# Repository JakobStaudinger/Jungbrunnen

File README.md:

# Jungbrunnen
An embedded project using a Raspberry Pi Pico to strobe LEDs to make it look like water droplets are floating in mid-air.
Heavily inspired by [isaac879's RGB Time Fountain](https://github.com/isaac879/RGB-Time-Fountain)

> [!WARNING]
> 🚧 Under development 🚧

## Firmware
Firmware for the cyw43 chip can be found [here](https://github.com/embassy-rs/embassy/tree/main/cyw43-firmware). It should be placed in the `cyw43-firmware` folder to make the program compile.

### Dev Firmware
To reduce the time it takes to flash the program to the Pico, you can enable the `dev_firmware` feature. This makes it so the firmware doesn't get embedded into the binary, and instead the program assumes it is already located at a fixed memory address.

You need to ensure the firmware is actually pre-baked into the flash memory. To do this, use the `probe-rs download` command, like so:
```console
$ probe-rs download cyw43-firmware/43439A0.bin --binary-format bin --chip RP2040 --base-address 0x10100000
$ probe-rs download cyw43-firmware/43439A0_clm.bin --binary-format bin --chip RP2040 --base-address 0x10140000
```

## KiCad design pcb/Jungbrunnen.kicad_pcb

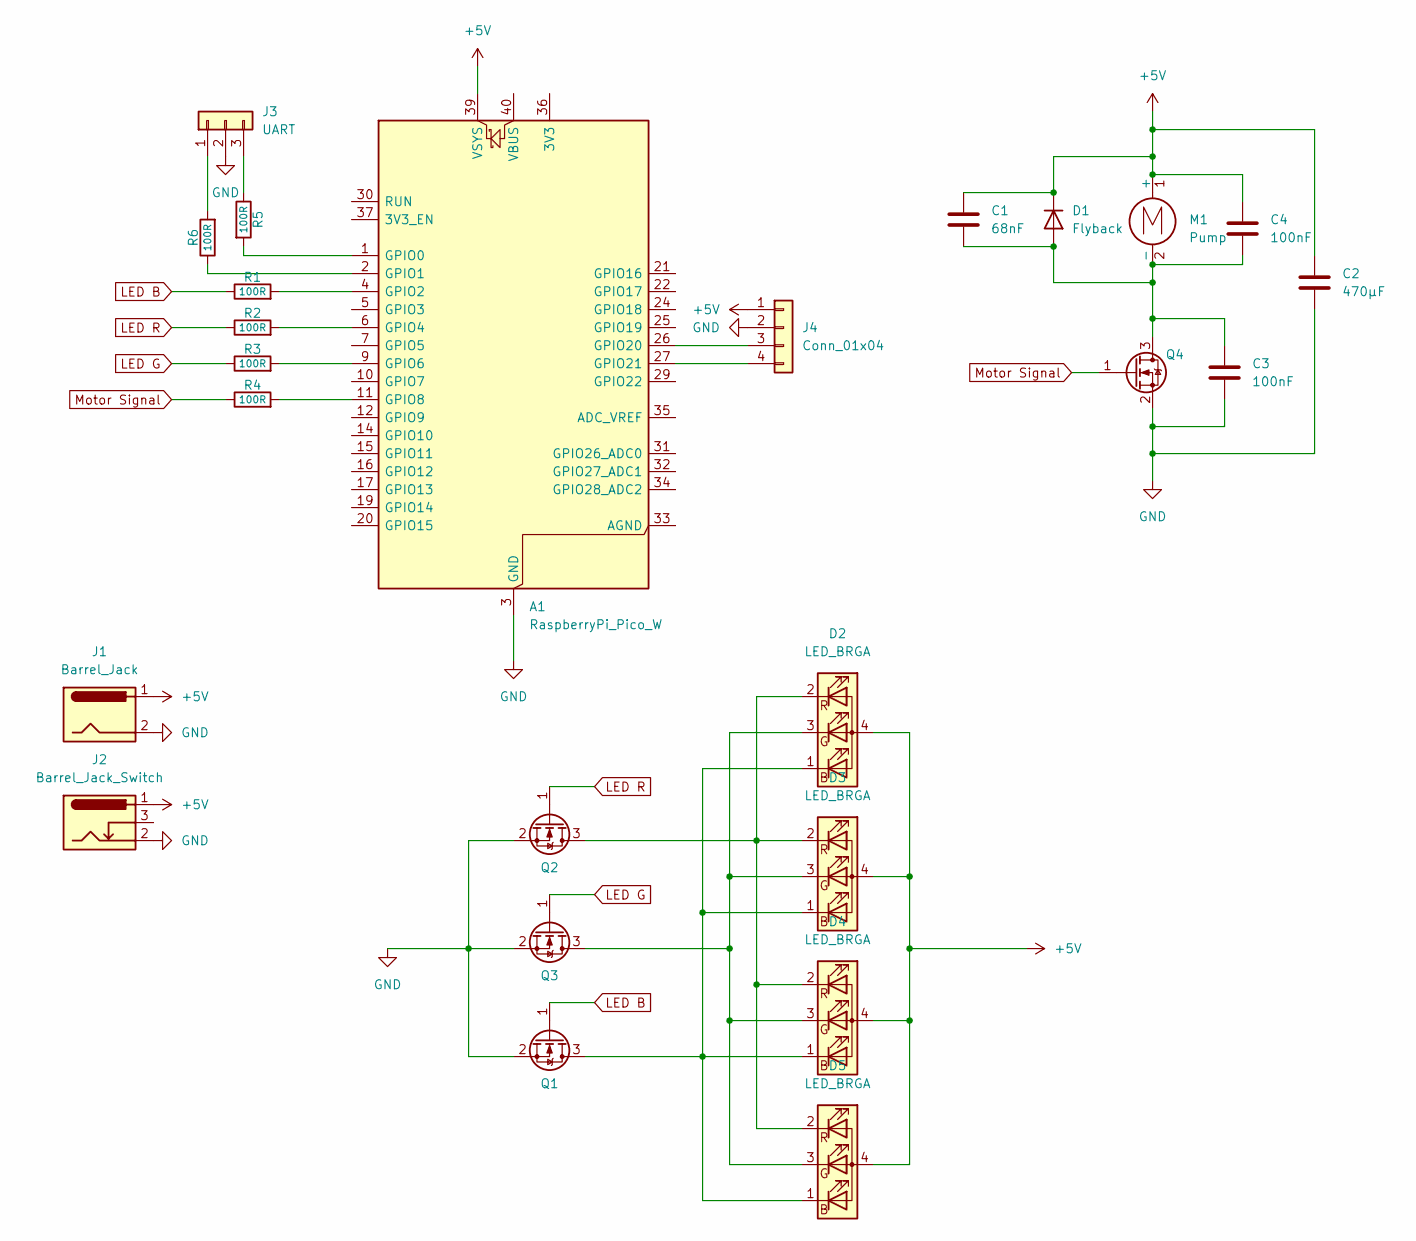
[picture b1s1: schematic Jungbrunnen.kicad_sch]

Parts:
A1: RaspberryPi_Pico_W; RaspberryPi_Pico_Common_THT
C1: 68nF; C_0805_2012Metric
C2: 470µF; C_Elec_8x10.2
C3, C4: 100nF; C_0805_2012Metric
D1: Flyback; D_SMA
D2, D3, D4, D5: LED_BRGA; JST_XH_B4B-XH-A_1x04_P2.50mm_Vertical
J1: Barrel_Jack; JST_XH_B2B-XH-A_1x02_P2.50mm_Vertical_Alternate
J2: Barrel_Jack_Switch; BarrelJack_Horizontal
J3: UART; JST_SH_SM03B-SRSS-TB_1x03-1MP_P1.00mm_Horizontal
J4: Conn_01x04; PinHeader_1x04_P2.54mm_Vertical
M1: Pump; JST_XH_B2B-XH-A_1x02_P2.50mm_Vertical_Alternate
Q1, Q2, Q3, Q4: AO3400A; SOT-23
R1, R2, R3, R4, R5, R6: 100R; R_0603_1608Metric

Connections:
+5V: A1.39 (VSYS), C1.1, C2.1, C4.1, D1.1 (K), D2.4 (A), D3.4 (A), D4.4 (A), D5.4 (A), J1.1, J2.1, J4.1, M1.1 (+)
GND: A1.3 (GND), A1.8 (GND), A1.13 (GND), A1.18 (GND), A1.23 (GND), A1.28 (GND), A1.38 (GND), C2.2, C3.2, J1.2, J2.2, J3.2, J4.2, Q1.2 (S), Q2.2 (S), Q3.2 (S), Q4.2 (S)
LED B: Q1.1 (G), R1.1
LED G: Q3.1 (G), R3.1
LED R: Q2.1 (G), R2.1
Motor Signal: Q4.1 (G), R4.1
unnamed: A1.1 (GPIO0), R5.2
unnamed: A1.2 (GPIO1), R6.1
unnamed: A1.4 (GPIO2), R1.2
unnamed: A1.6 (GPIO4), R2.2
unnamed: A1.9 (GPIO6), R3.2
unnamed: A1.11 (GPIO8), R4.2
unnamed: A1.26 (GPIO20), J4.3
unnamed: A1.27 (GPIO21), J4.4
unnamed: C1.2, C3.1, C4.2, D1.2 (A), M1.2 (-), Q4.3 (D)
unnamed: D2.1 (BK), D3.1 (BK), D4.1 (BK), D5.1 (BK), Q1.3 (D)
unnamed: D2.3 (GK), D3.3 (GK), D4.3 (GK), D5.3 (GK), Q3.3 (D)
unnamed: D2.2 (RK), D3.2 (RK), D4.2 (RK), D5.2 (RK), Q2.3 (D)
unnamed: J3.1, R6.2
unnamed: J3.3, R5.1

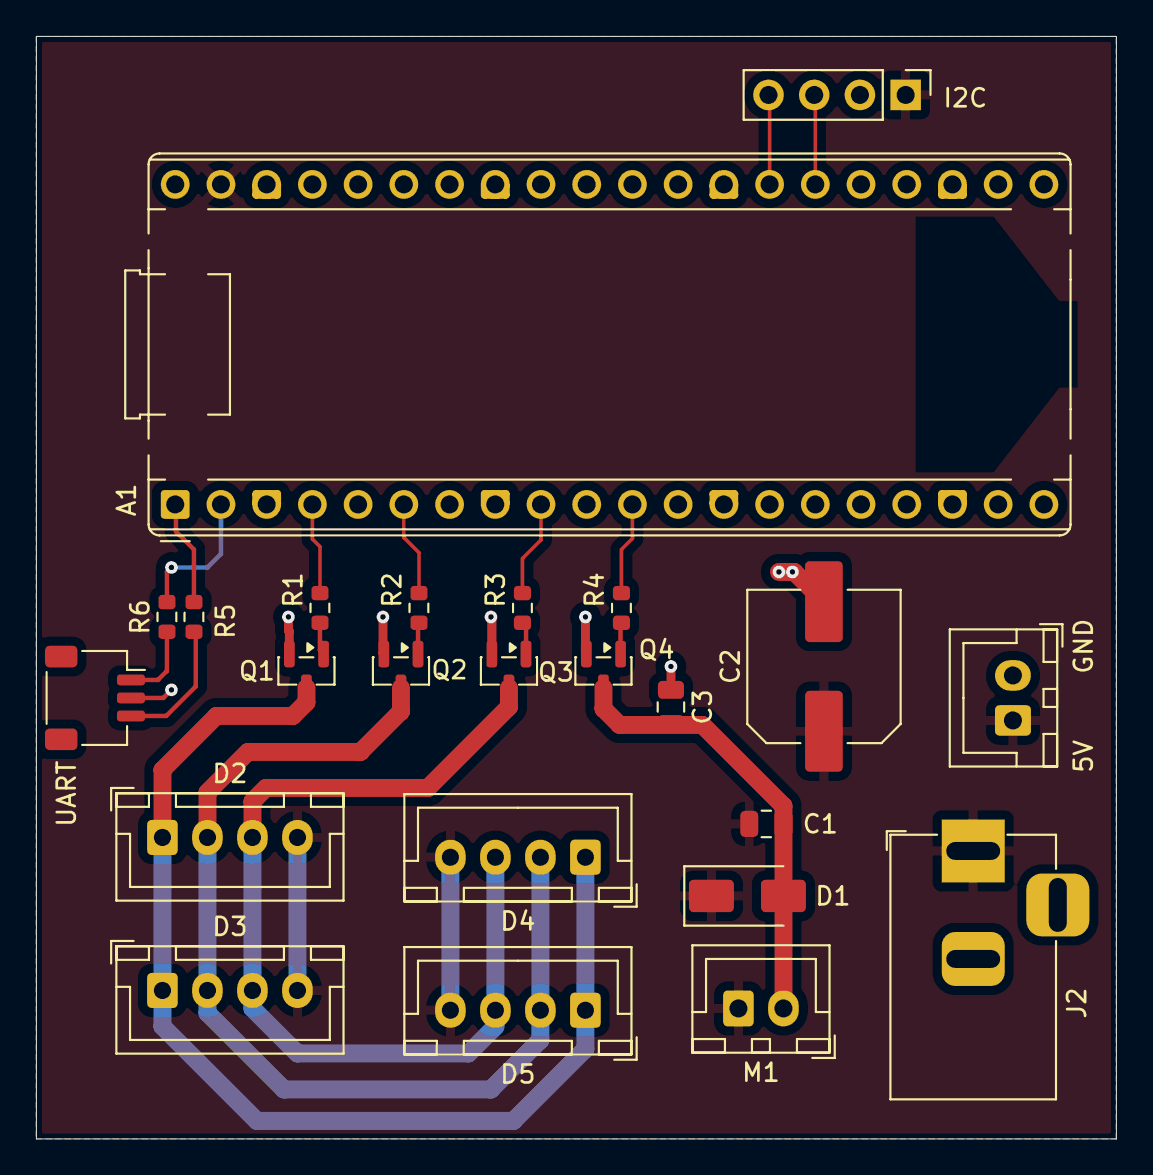
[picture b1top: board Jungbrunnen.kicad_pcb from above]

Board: 2 copper layers, 60.0 x 61.2 mm, 24 parts (0 on the bottom side), 20 nets.

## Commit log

2025-08-10 implement hello-world of PIO
2025-09-04 WIP: Implement strobing of LEDs
2025-09-05 control LEDs with PIO
2025-09-06 support multiple color streams
2025-09-20 extract code into separate file
2025-10-12 refactor: move LED orchestration into separate task
2025-10-12 chore: rename
2025-10-25 refactor: move modules to subfolders
2025-10-25 chore: update dependencies
2025-11-01 feat: add PCB designs
2025-11-02 feat: add network capabilities
2025-11-02 fix: stop stuttering when calculating next batch of color values
2025-11-02 feat: add MQTT boilerplate
